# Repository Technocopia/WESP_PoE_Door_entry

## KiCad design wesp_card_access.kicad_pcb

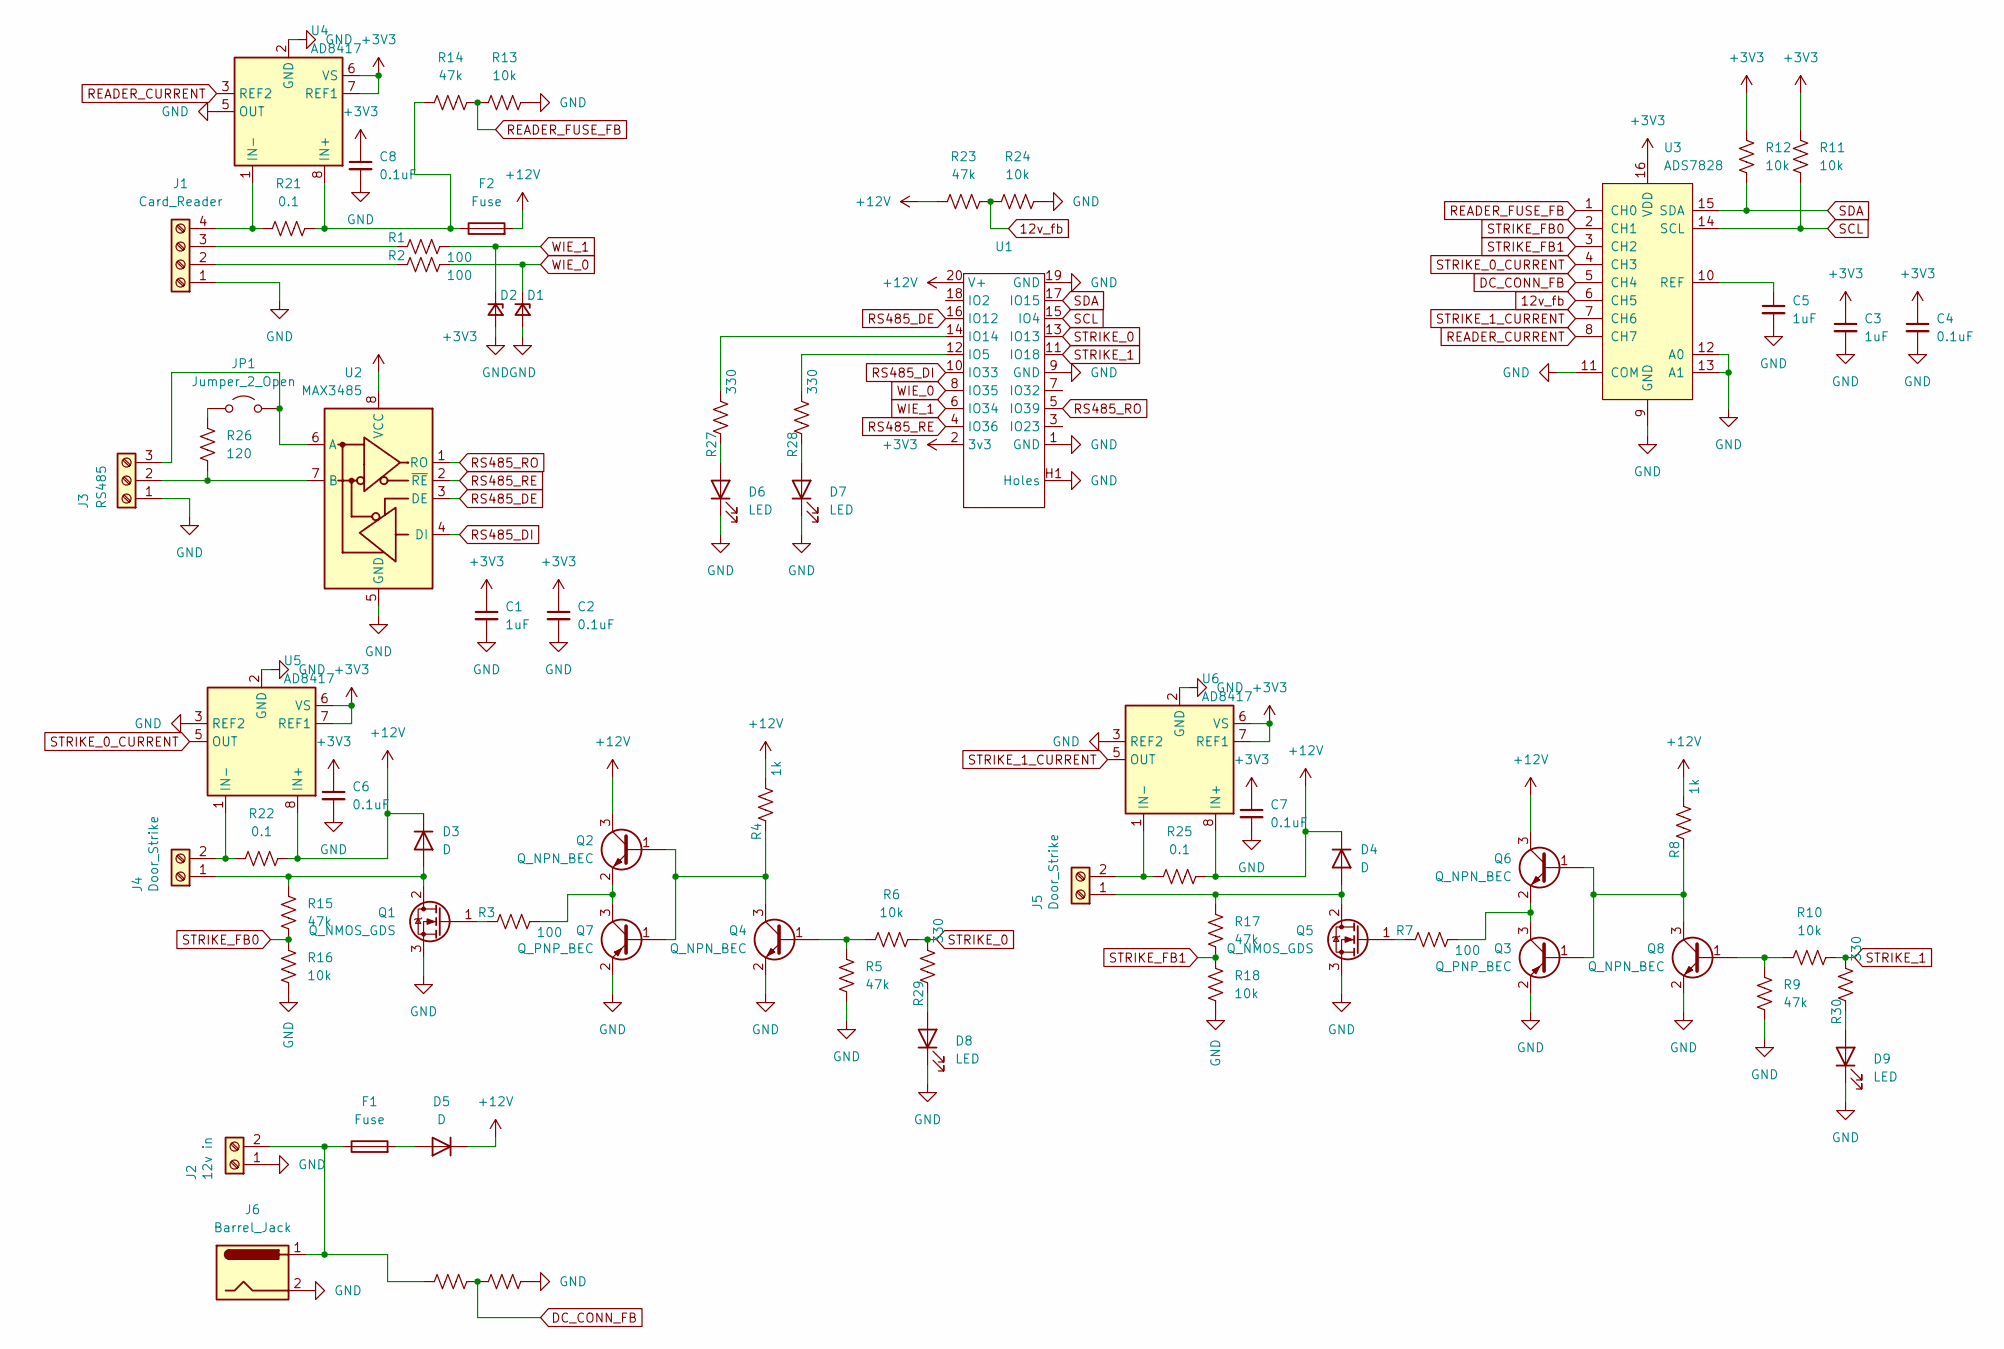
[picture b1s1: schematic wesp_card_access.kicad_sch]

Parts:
C1, C3, C5: 1uF; C_0603_1608Metric
C2, C4, C6, C7, C8: 0.1uF; C_0603_1608Metric
D1, D2: D_Zener_Small; D_SMA
D3, D4, D5: D; D_SMA
D6, D7, D8, D9: LED; LED_0603_1608Metric
F1, F2: Fuse; 0154Series_LTF
J1: Card_Reader; PhoenixContact_MC_1,5_4-G-3.81_1x04_P3.81mm_Horizontal
J2: 12v in; PhoenixContact_MC_1,5_2-G-3.81_1x02_P3.81mm_Horizontal
J3: RS485; PhoenixContact_MC_1,5_3-G-3.81_1x03_P3.81mm_Horizontal
J4, J5: Door_Strike; PhoenixContact_MC_1,5_2-G-3.81_1x02_P3.81mm_Horizontal
J6: Barrel_Jack; BarrelJack_Horizontal
JP1: Jumper_2_Open; SolderJumper-2_P1.3mm_Open_TrianglePad1.0x1.5mm
Q1, Q5: Q_NMOS_GDS; TO-252-2
Q2, Q4, Q6, Q8: Q_NPN_BEC; SOT-23
Q3, Q7: Q_PNP_BEC; SOT-23
R1, R2, R3, R7: 100; R_0603_1608Metric
R4, R8: 1k; R_0603_1608Metric
R5, R9, R14, R15, R17, R19, R23: 47k; R_0603_1608Metric
R6, R10, R11, R12, R13, R16, R18, R20, R24: 10k; R_0603_1608Metric
R21, R22, R25: 0.1; R_0805_2012Metric
R26: 120; R_0805_2012Metric
R27, R28, R29, R30: 330; R_0603_1608Metric
U1: wesp_hat
U2: MAX3485; SOIC-8_3.9x4.9mm_P1.27mm
U3: ADS7828; TSSOP-16_4.4x5mm_P0.65mm
U4, U5, U6: AD8417; MSOP-8_3x3mm_P0.65mm

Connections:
12v_fb: R23.1, R24.1, U3.6 (CH5)
+3V3: C1.1, C2.1, C3.1, C4.1, C6.1, C7.1, C8.1, R11.2, R12.2, U1.2 (3v3), U2.8 (VCC), U3.16 (VDD), U4.6 (VS), U4.7 (REF1), U5.6 (VS), U5.7 (REF1), U6.6 (VS), U6.7 (REF1)
+12V: D3.1 (K), D4.1 (K), D5.1 (K), F2.2, Q2.3 (C), Q6.3 (C), R4.2, R8.2, R22.1, R23.2, R25.1, U1.20 (V+), U5.8 (IN+), U6.8 (IN+)
DC_CONN_FB: R19.1, R20.1, U3.5 (CH4)
GND: C1.2, C2.2, C3.2, C4.2, C5.2, C6.2, C7.2, C8.2, D1.2 (A), D2.2 (A), D6.1 (K), D7.1 (K), D8.1 (K), D9.1 (K), J1.1, J2.1, J3.1, J6.2, Q1.3 (S), Q3.2 (E), Q4.2 (E), Q5.3 (S), Q7.2 (E), Q8.2 (E), R5.2, R9.2, R13.2, R16.2, R18.2, R20.2, R24.2, U1.1 (GND), U1.9 (GND), U1.19 (GND), U1.H1 (Holes), U2.5 (GND), U3.9 (GND), U3.11 (COM), U3.12 (A0), U3.13 (A1), U4.2 (GND), U4.5 (OUT), U5.2 (GND), U5.3 (REF2), U6.2 (GND), U6.3 (REF2)
unnamed: D3.2 (A), J4.1, Q1.2 (D), R15.2
unnamed: D4.2 (A), J5.1, Q5.2 (D), R17.2
unnamed: D5.2 (A), F1.2
unnamed: D6.2 (A), R27.1
unnamed: D7.2 (A), R28.1
unnamed: D8.2 (A), R29.1
unnamed: D9.2 (A), R30.1
unnamed: J1.2, R2.1
unnamed: J1.3, R1.1
unnamed: J1.4, R21.2, U4.1 (IN-)
unnamed: F1.1, J2.2, J6.1, R19.2
unnamed: J3.2, R26.2, U2.7 (B)
unnamed: J3.3, JP1.2 (B), U2.6 (A)
unnamed: J4.2, R22.2, U5.1 (IN-)
unnamed: J5.2, R25.2, U6.1 (IN-)
unnamed: JP1.1 (A), R26.1
unnamed: Q1.1 (G), R3.1
unnamed: Q2.1 (B), Q4.3 (C), Q7.1 (B), R4.1
unnamed: Q2.2 (E), Q7.3 (C), R3.2
unnamed: Q3.1 (B), Q6.1 (B), Q8.3 (C), R8.1
unnamed: Q3.3 (C), Q6.2 (E), R7.2
unnamed: Q4.1 (B), R5.1, R6.1
unnamed: Q5.1 (G), R7.1
unnamed: Q8.1 (B), R9.1, R10.1
unnamed: R28.2, U1.12 (IO5)
unnamed: R27.2, U1.14 (IO14)
unnamed: C5.1, U3.10 (REF)
unnamed: F2.1, R14.2, R21.1, U4.8 (IN+)
READER_CURRENT: U3.8 (CH7), U4.3 (REF2)
READER_FUSE_FB: R13.1, R14.1, U3.1 (CH0)
RS485_DE: U1.16 (IO12), U2.3 (DE)
RS485_DI: U1.10 (IO33), U2.4 (DI)
RS485_RE: U1.4 (IO36), U2.2 (~RE)
RS485_RO: U1.5 (IO39), U2.1 (RO)
SCL: R11.1, U1.15 (IO4), U3.14 (SCL)
SDA: R12.1, U1.17 (IO15), U3.15 (SDA)
STRIKE_0: R6.2, R29.2, U1.13 (IO13)
STRIKE_0_CURRENT: U3.4 (CH3), U5.5 (OUT)
STRIKE_1: R10.2, R30.2, U1.11 (IO18)
STRIKE_1_CURRENT: U3.7 (CH6), U6.5 (OUT)
STRIKE_FB0: R15.1, R16.1, U3.2 (CH1)
STRIKE_FB1: R17.1, R18.1, U3.3 (CH2)
WIE_0: D1.1 (K), R2.2, U1.8 (IO35)
WIE_1: D2.1 (K), R1.2, U1.6 (IO34)

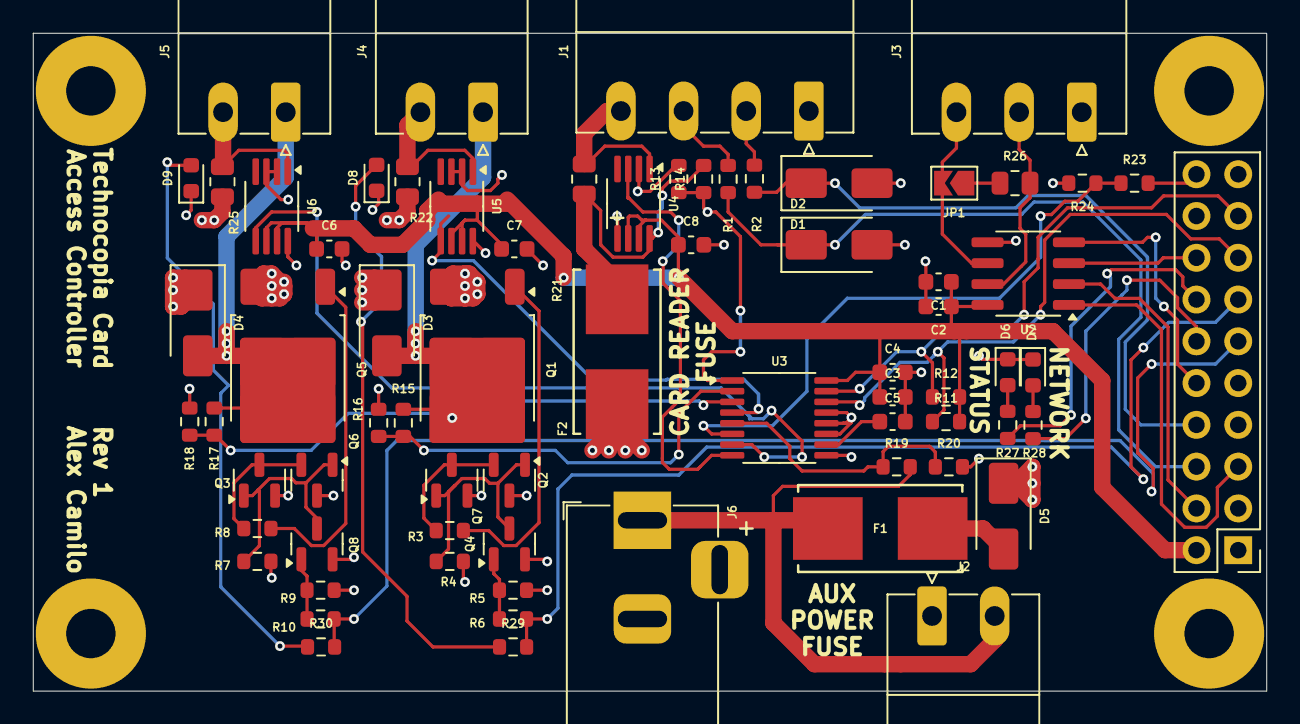
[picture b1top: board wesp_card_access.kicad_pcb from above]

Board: 4 copper layers, 75.0 x 40.0 mm, 70 parts (0 on the bottom side), 49 nets.
